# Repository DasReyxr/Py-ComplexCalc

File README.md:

# Py-ComplexCalc

**A complete ecosystem for solving n×n complex linear systems (Ax=b)** with both desktop GUI and embedded hardware solutions.

**Solve Ax=b instantly** with dual-format output (polar & rectangular), flexible input, and full system persistence.

```
Py-ComplexCalc/
├── Software Version/          # Desktop GUI application
│   ├── code/                  # Python source files
│   │   ├── UI_ComplexCalc.py  # Main GUI (customtkinter)
│   │   ├── ComplexCalc.py     # Core solver & parsing logic
│   │   ├── HK.jpg             # UI background
│   │   └── IE.png             # Logo icon
│   ├── doc/                   # Documentation
│   └── README.md              # Software-specific guide
│
├── HW Version/                # Embedded microcontroller solutions
│   ├── code/
│   │   ├── BlackPill STM32F411CE/    # Implementation for BlackPill
│   │   └── RayPill STM32F446ZE/      # Implementation for RayPill
│   ├── HW Files Schematic & Design/  # PCB schematics, layouts
│   └── (README coming soon)
│
├── OtherCalcs/                # Alternative implementations
├── LICENSE                    # MIT License
└── README.md          # This file
```

## ✨ Features

- **🔢 Dual Input Format**
  - Rectangular: `3+4j`, `-j2`, `5` (supports both `i` and `j` for imaginary unit)
  - Phasor: `10L30`, `5L-90°`, `3L0` (polar notation with degree angles)
  - Mix both formats in the same system
- **📊 Dual-Format Output**
  - Solutions shown in **polar** and **rectangular** simultaneously
- **🌓 Multiple Themes**
  - Dark, Light, Pink, Mint, Purple, Ocean — toggle anytime
- **💾 System Persistence**
  - Auto-save/load all computed systems
  - **File menu**: save current system, import from file, load saved system, refresh list
  - Export results (`.py`, `.txt`)
  - Session history with timestamps
- **🎯 Dynamic Matrix Sizing**
  - Solve 1×1 up to 10×10 systems
- **🧮 Built-in Calculator**
  - Quick complex-number scratchpad with backspace support
- **🚀 Standalone Executables**
  - Windows `.exe` and Linux binary — no Python install needed (see [Releases](https://github.com/DasReyxr/Py-ComplexCalc/releases))

---

## ℹ️ About

| | |
|---|---|
| **Version** | 4.00 |
| **Last updated** | 2026-08-21 |
| **Repository** | [github.com/DasReyxr/Py-ComplexCalc](https://github.com/DasReyxr/Py-ComplexCalc) |
| **Institution** | Universidad Autónoma de Aguascalientes |
| **Department** | Ingeniería en Electrónica |

Also available inside the app itself: **Help → About Complex Calc...**

---

## 🚀 Quick Start

### Option 1: Standalone Executable

1. Download `UI_ComplexCalc.exe` (Windows) or `UI_ComplexCalc` (Linux) from the latest [Release](https://github.com/DasReyxr/Py-ComplexCalc/releases).
2. Run it directly. No dependencies needed.

### Option 2: Run from Source

**Requirements:** Python 3.8+ (tested on 3.10, 3.11)

```bash
# Clone the repo
git clone https://github.com/DasReyxr/Py-ComplexCalc.git
cd Py-ComplexCalc/code

# (Optional) Create virtual environment
python -m venv .venv
source .venv/bin/activate  # Linux/macOS
# or: .\.venv\Scripts\Activate  # Windows PowerShell

# Install dependencies
pip install -r requirements.txt

# Run the app
python UI_ComplexCalc.py
```

---

## 📝 Input Format Guide

| Format         | Examples         | Notes                                 |
|---------------|------------------|---------------------------------------|
| Rectangular   | `3+4j`, `-j2`, `5` | Supports `i` and `j` for imaginary unit |
| Phasor        | `10L30`, `5L-90°`, `3L0` | Polar notation, degree angles         |
| Mixed         | Any combination   | Rows/columns can mix formats          |

### Example: Solving a 3×3 Complex System

**Problem:** Solve Ax = b where:
```
A = [2+1i    -1      0   ]      b = [1  ]
    [-1    2+0.5i  -1  ]          [0  ]
    [0      -1      2   ]          [1i ]
```

**Steps:**
1. Launch the app
2. Select **3×3** from size dropdown
3. Enter matrix A and vector b values (any format)
4. Click **Solve**
5. View results in both forms

**Output:**
```
x₁ = 0.8 + 0.6j  (Rectangular)
   = 1.0 ∠ 36.87° (Polar)

x₂ = 0.4 + 0.2j
   = 0.447 ∠ 26.57°

x₃ = 0.2 - 0.4j
   = 0.447 ∠ -63.43°
```

---

## 🛠️ Building a Standalone Executable (Windows & Linux)

PyInstaller builds a native executable for whatever OS you run it on — it
does **not** cross-compile, so a Windows `.exe` must be built on Windows
and a Linux binary must be built on Linux. This repo's GitHub Actions
workflow (`.github/workflows/build.yml`) does both automatically — trigger
it manually from the **Actions** tab, or push a tag like `v4.1` to also
publish a Release.

To build locally:

```bash
pip install pyinstaller
cd code
pyinstaller UI_ComplexCalc.spec
# Output: code/dist/UI_ComplexCalc(.exe on Windows)
```

---

## 📂 Project Structure

```
Py-ComplexCalc/
├── code/
│   ├── UI_ComplexCalc.py      # Main GUI (customtkinter)
│   ├── ComplexCalc.py         # Core solver & parsing logic
│   ├── UI_ComplexCalc.spec    # PyInstaller build spec
│   ├── requirements.txt       # Python dependencies
│   ├── HK.jpg                 # UI background / window icon
│   ├── IE.png                 # Institution logo
│   └── themes.json            # Color theme definitions
├── tests/
│   └── test_complexcalc_core.py  # Parser/solver robustness tests
├── doc/                        # Manuals
├── images/                     # README screenshots
└── LICENSE
```

---

## 🧪 Tests

Robustness tests for the parser, solver and persistence core (malformed
input, singular matrices, out-of-range sizes) — no extra dependencies:

```bash
python3 -m unittest discover -s tests -v
```

---

## 📋 Dependencies

| Package         | Purpose                                 |
|-----------------|-----------------------------------------|
| `numpy`         | Linear algebra (Gaussian elimination)   |
| `customtkinter` | Modern, theme-aware GUI widgets         |
| `pillow`        | Image loading for UI assets             |

**Install all at once:**
```bash
pip install -r code/requirements.txt
```

---

## 🎨 Customization

- **Change Theme Colors:** Edit `code/themes.json`.
- **Custom Images:** Replace `HK.jpg` and `IE.png` with your own (same filenames).

---

## 🐛 Troubleshooting

| Problem                    | Solution                                                        |
|----------------------------|-----------------------------------------------------------------|
| GUI won't start            | Install/upgrade customtkinter: `pip install --upgrade customtkinter` |
| "Singular matrix" error    | Matrix A must be invertible. Check for duplicate/linearly dependent rows. |
| Parsing error              | Use `3+4j` (no spaces), `10L30` (not `10L30.5`).                |
| Images not loading         | Ensure `HK.jpg` and `IE.png` exist in the same folder as `UI_ComplexCalc.py`. |
| Executable blocked by antivirus | False positive (Windows). Add to antivirus whitelist or build from source. |

---

## 📞 Support & Contributions

- **Bug Reports:** [GitHub Issues](https://github.com/DasReyxr/Py-ComplexCalc/issues)
- **Feature Requests:** [GitHub Discussions](https://github.com/DasReyxr/Py-ComplexCalc/discussions)
- **Pull Requests:** Welcome! Fork, branch, and submit a PR.

### Roadmap
- [ ] CSV import/export for batch solving
- [ ] Phasor diagram real-time visualization
- [ ] Advanced matrix operations (eigenvalues, determinants)

---

## 👥 Credits

**Developers:**
- Iker Garcia — [ikergarcia450@gmail.com](mailto:ikergarcia450@gmail.com)
- Das Reyes — [das.reyxr@outlook.com](mailto:das.reyxr@outlook.com)

**Development Team:**
- **Das Reyes** — Lead developer, theming, Testing, documentation [das.reyxr@outlook.com](mailto:das.reyxr@outlook.com)
- **Iker Garcia** — GUI design, user experience, documentation [ikergarcia450@gmail.com](mailto:ikergarcia450@gmail.com)
- **Roberto Lopez** — PCB Design, core solver logic  
- **Kevin Lara** — Hardware integration, embedded systems

**Built With:**
- [NumPy](https://numpy.org/) — Numerical computing
- [CustomTkinter](https://github.com/TomSchimansky/CustomTkinter) — Modern UI toolkit
- [Pillow](https://python-pillow.org/) — Image processing
- [PyInstaller](https://pyinstaller.org/) — Executable packaging

---

## 📄 License

MIT License — See [LICENSE](./LICENSE) for details.

**TL;DR:** Use freely, attribute the authors, no warranty.

---

**For Electronics Engineers, By Electronics Engineers** ⚡

*"Solve complex systems instantly. Focus on the engineering that matters."*

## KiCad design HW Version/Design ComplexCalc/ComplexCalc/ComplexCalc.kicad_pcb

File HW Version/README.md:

# Hardware Version 🔌⚡

**Embedded n×n complex linear system solver for STM32 microcontrollers.**

Real-time computation of Ax=b problems directly on ARM-based hardware, perfect for **AC circuit analysis, impedance calculations, and embedded signal processing**.

---

## 🎯 Overview

This folder contains complete hardware implementations for solving complex linear systems on microcontroller platforms, with no external dependencies or desktop PC required.

**Key Advantages:**
- ⚡ Real-time computation on embedded hardware
- 💾 Onboard persistent storage
- 🔋 Low power consumption

---

## 📋 Supported Platforms

### **BlackPill STM32F411CE** ✅
```
📁 BlackPill STM32F411CE/

Platform Details:
├─ MCU: ARM Cortex-M4 @ 100 MHz
├─ RAM: 128 KB
├─ Flash: 512 KB
├─ USB: Full-Speed (480 Mbps)
├─ Peripherals: ADC, UART, SPI, I2C
├─ Typical Use: Budget-conscious, compact designs
└─ Status: Fully implemented ✓
```

**Perfect for:**
- Portable embedded instruments
- Compact circuit analysis tools
- Educational projects with size constraints
- Low-cost mass production

---

### **RayPill STM32F446ZE** 🔄
```
📁 RayPill STM32F446ZE/

Platform Details:
├─ MCU: ARM Cortex-M4 @ 180 MHz
├─ RAM: 192 KB
├─ Flash: 512 KB
├─ USB: High-Speed (480 Mbps)
├─ Peripherals: Multiple ADCs, UARTs, SPI, I2C, Ethernet
├─ Typical Use: High-performance applications
└─ Status: Fully implemented ✓
```

**Perfect for:**
- Multi-channel signal processing
- High-speed real-time systems
- Industrial instrumentation
- Network-connected devices

---

## 🚀 Quick Start

### **Step 1: Choose Your Platform**
- **Limited resources?** → BlackPill STM32F411CE
- **Need more power?** → RayPill STM32F446ZE

### **Step 2: Get the Code**
```bash
cd HW\ Version/code/BlackPill\ STM32F411CE/
# or
cd HW\ Version/code/RayPill\ STM32F446ZE/
```

### **Step 3: Build & Flash**

**Using STM32CubeIDE (Recommended):**
1. Open STM32CubeIDE
2. File → Open Projects from File System
3. Select the platform folder
4. Press `Build` (Ctrl+B)
5. Connect microcontroller via USB
6. Press `Run` (Ctrl+Alt+X) to flash

**Using Arm Compiler Toolchain:**
```bash
arm-none-eabi-gcc -mcpu=cortex-m4 -mthumb \
  -O2 -Wall -c main.c -o main.o

arm-none-eabi-ld main.o -o firmware.elf

arm-none-eabi-objcopy -O binary firmware.elf firmware.bin
```

### **Step 4: Connect & Use**

**Via UART (Serial Terminal):**
```
Device: COM3 (Windows) or /dev/ttyUSB0 (Linux)
Baud Rate: 115200
Data Bits: 8
Parity: None
Stop Bits: 1
Flow Control: None
```

---

## 📂 Folder Structure

```
HW Version/
├── code/
│   ├── BlackPill STM32F411CE/
│   │   ├── main.c                # Entry point
│   │   ├── solver.c/.h           # Linear solver implementation
│   │   ├── parser.c/.h           # Complex number parser
│   │   ├── uart_io.c/.h          # Serial communication
│   │   ├── storage.c/.h          # Persistent memory
│   │   ├── STM32F411_HAL.conf    # Cube configuration
│   │   └── Makefile
│   │
│   └── RayPill STM32F446ZE/
│       ├── main.c
│       ├── solver.c/.h
│       ├── parser.c/.h
│       ├── uart_io.c/.h
│       ├── storage.c/.h
│       ├── STM32F446_HAL.conf
│       └── Makefile
│
├── HW Files Schematic & Design/
│   ├── Schematics/               # KiCad/.pdf circuit diagrams
│   ├── PCB Layouts/              # Gerber files for manufacturing
│   ├── BOM.csv                   # Bill of Materials
│   └── Assembly Guide.md         # PCB assembly instructions
│
└── README.md                     # This file
```

---

## 🔧 Technical Details

### **Solver Algorithm**
- **Method:** Gaussian elimination with partial pivoting
- **Precision:** Double-precision floating-point (64-bit)
- **Maximum Size:** 10×10 systems (configurable)
- **Computation Time:** ~10-50 ms (BlackPill), ~5-25 ms (RayPill)

### **Input Format Support**
| Format | Example | Supported |
|--------|---------|-----------|
| **Rectangular** | `3+4j`, `-j2`, `5` | ✅ Yes |
| **Phasor** | `10L30`, `5L-90°` | ✅ Yes |
| **Mixed** | Both in same system | ✅ Yes |

### **Output Format**
Results automatically convert to:
- **Rectangular:** `a + bj` (real + imaginary parts)

---

## 🛠️ Hardware Requirements

### **Minimum Setup**

**For BlackPill:**
- 1× BlackPill STM32F411CE board
- 1× USB-C cable (power & programming)
- 1× Serial terminal software (PuTTY, Tera Term, etc.)

**For RayPill:**
- 1× RayPill STM32F446ZE board
- 1× USB-A cable (power & programming)
- 1× Serial terminal software
- Optional: Additional sensors/peripherals

### **Optional Accessories**
- Logic analyzer (debugging)
- Oscilloscope (signal verification)
- SWD debugger (advanced debugging)

---

## 🚨 Troubleshooting

### **Build Issues**

| Problem | Solution |
|---------|----------|
| **"arm-none-eabi-gcc not found"** | Install ARM GCC toolchain for your OS |
| **Cannot connect to CubeIDE** | Ensure STM32CubeIDE is installed with F4 MCU support |
| **Build errors in HAL** | Verify STM32CubeMX generated files match target MCU |

### **Runtime Issues**

| Problem | Solution |
|---------|----------|
| **No serial output** | Check UART pins & baud rate (115200) |
| **"Singular matrix" error** | Matrix A must be invertible; add small diagonal term if needed |
| **Parsing error on input** | Use format `3+4j` (no spaces), `10L30` (not degrees symbol) |
| **System won't flash** | Ensure USB cable supports data transfer; try different port |

---

## 📊 Performance Comparison

| Metric | BlackPill F411 | RayPill F446 |
|--------|----------------|--------------|
| **Clock Speed** | 100 MHz | 180 MHz |
| **RAM** | 128 KB | 192 KB |
| **Flash** | 512 KB | 512 KB |
| **Solve Time (3×3)** | ~25 ms | ~12 ms |
| **Solve Time (10×10)** | ~200 ms | ~80 ms |
| **USB Speed** | Full-Speed | High-Speed |
| **Power Draw** | ~25 mA idle | ~45 mA idle |

---

## 🔌 Pinout Reference

## 📚 Additional Resources

- **[STM32F411 Datasheet](https://www.st.com/resource/en/datasheet/stm32f411ce.pdf)** — Complete hardware specs
- **[STM32F446 Datasheet](https://www.st.com/resource/en/datasheet/stm32f446ze.pdf)** — Complete hardware specs
- **[STM32CubeIDE Setup Guide](https://www.st.com/en/development-tools/stm32cubeide.html)** — IDE download & installation
- **[ARM CMSIS-DSP Library](https://github.com/ARM-software/CMSIS_5)** — Optimized math library
- **[Keil Compiler Documentation](https://www2.keil.com/mdk5)** — ARM compiler details

---

## 🐛 Known Limitations

- **Matrix Size:** Limited to 10×10 by design (RAM constraint on BlackPill)
- **Precision:** Double-precision (64-bit) floating-point accuracy
- **Complex Numbers:** No quaternions or higher algebras (future feature)
- **Visualization:** No built-in display output 

---

## 🤝 Contributing

Want to add support for more platforms? We'd love your help!

**How to contribute:**
1. Create a new folder: `code/YourMCU_Name/`
2. Implement `solver.c`, `parser.c`, `uart_io.c`, `storage.c`
3. Add build instructions and testing results
4. Submit a pull request with documentation

**Planned Goals:**
- [ ] Support for STM32F
- [ ] Optimize the code
- [ ] Clean the code
- [ ] Compile the Hex for easy uploading
- [ ] Upload the Designing files (Open Hardware) 

---

## 📞 Support & Issues

- **Bug Reports:** [GitHub Issues](https://github.com/DasReyxr/Py-ComplexCalc/issues)
- **Hardware Questions:** Open an issue with `[HARDWARE]` tag
- **Schematics:** Check `HW Files Schematic & Design/`
- **Build Help:** Include your MCU, IDE, and error message

---

## 📄 License

MIT License — See [../LICENSE](../LICENSE) for details.

---

## 🎯 Quick Links

| Resource | Location |
|----------|----------|
| **Main README** | [../README_GENERAL.md](../README_GENERAL.md) |
| **Software Version** | [../Software%20Version/](../Software%20Version/) |
| **Schematics** | [HW%20Files%20Schematic%20&%20Design/](HW%20Files%20Schematic%20%26%20Design/) |
| **GitHub** | [DasReyxr/Py-ComplexCalc](https://github.com/DasReyxr/Py-ComplexCalc) |

---

**For Electronics Engineers, By Electronics Engineers** ⚡

*"Embedded linear algebra solver. No PC required."*

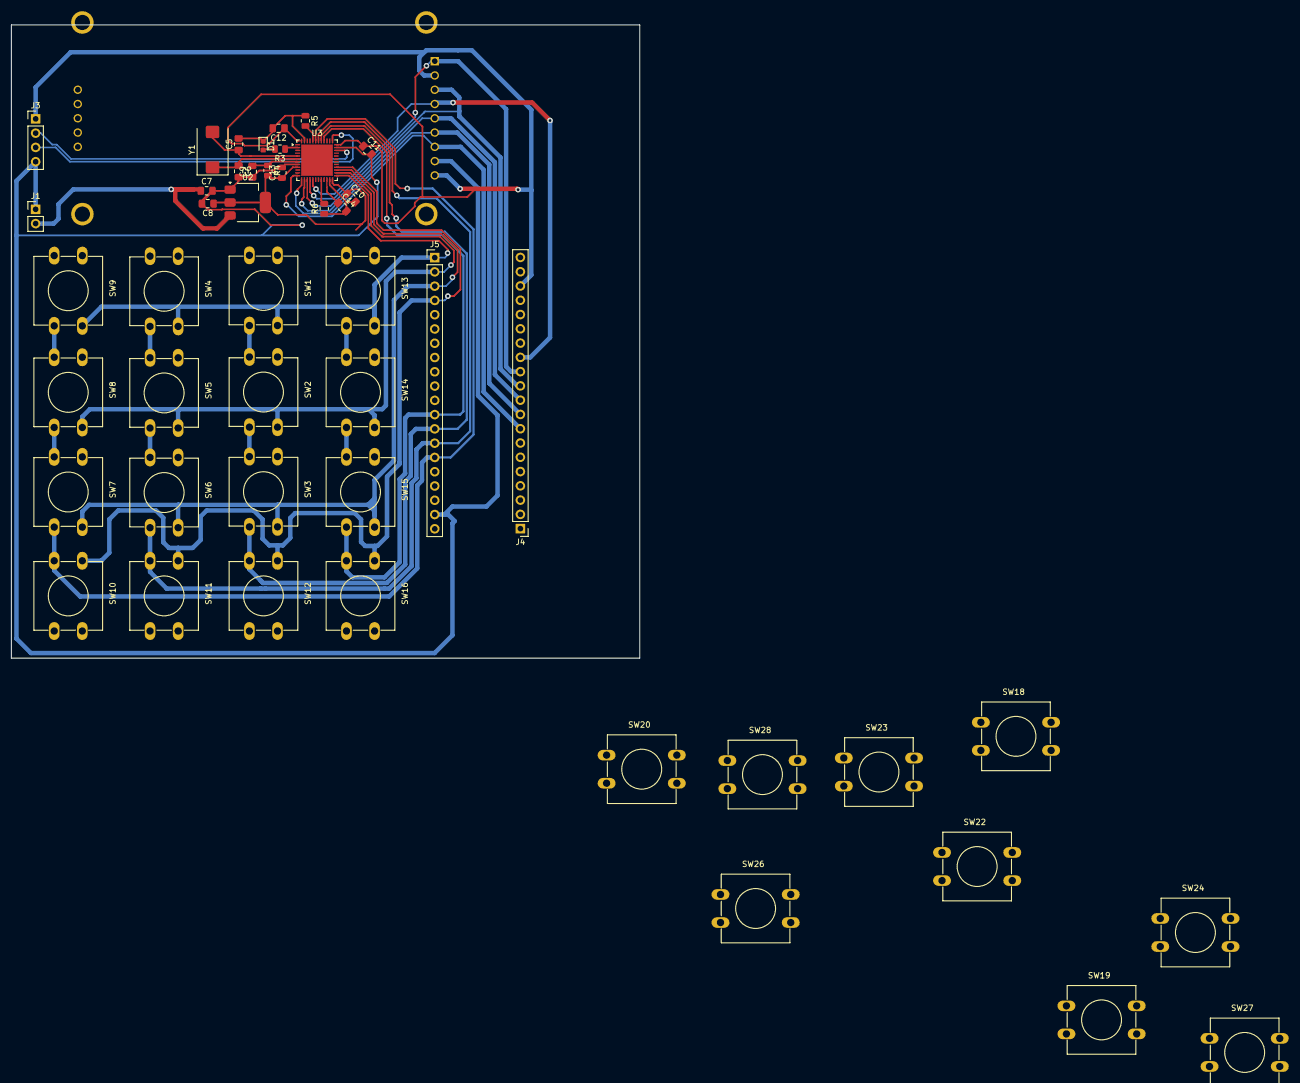
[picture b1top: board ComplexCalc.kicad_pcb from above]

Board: 2 copper layers, 111.8 x 112.7 mm, 48 parts (1 on the bottom side), 46 nets.

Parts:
C5, C6: 22pF; C_0805_2012Metric_Pad1.18x1.45mm_HandSolder
C7: 10uF; C_0805_2012Metric_Pad1.18x1.45mm_HandSolder
C8: 22uF; C_0805_2012Metric_Pad1.18x1.45mm_HandSolder
C9: 1uF; C_0805_2012Metric_Pad1.18x1.45mm_HandSolder
C10, C11, C12: 100nF; C_0805_2012Metric_Pad1.18x1.45mm_HandSolder
C13: 1uF; C_0805_2012Metric
C14: 2.2uF; C_0805_2012Metric_Pad1.18x1.45mm_HandSolder
D1: LED; LED_0603_1608Metric
J1: V_Battery; PinHeader_1x02_P2.54mm_Vertical
J2: Conn_01x09; CR2013-MI2120
J3: STLINK; PinHeader_1x04_P2.54mm_Vertical
J4, J5: Conn_01x20_Socket; PinHeader_1x20_P2.54mm_Vertical
R3: 220; R_0805_2012Metric
R4, R5, R6: 10k; R_0805_2012Metric
SW1: 4; SW_PUSH-12mm
SW2: 5; SW_PUSH-12mm
SW3: 6; SW_PUSH-12mm
SW4: 1; SW_PUSH-12mm
SW5: 2; SW_PUSH-12mm
SW6: 3; SW_PUSH-12mm
SW7: =; SW_PUSH-12mm
SW8: .; SW_PUSH-12mm
SW9: 0; SW_PUSH-12mm
SW10: -; SW_PUSH-12mm
SW11: del; SW_PUSH-12mm
SW12: <-; SW_PUSH-12mm
SW13: 7; SW_PUSH-12mm
SW14: 8; SW_PUSH-12mm
SW15: 9; SW_PUSH-12mm
SW16: M; SW_PUSH-12mm
SW18, SW20, SW26, SW28: MOD; SW_PUSH-12mm
SW19: <; SW_PUSH-12mm
SW22: ^; SW_PUSH-12mm
SW23: OK; SW_PUSH-12mm
SW24: v; SW_PUSH-12mm
SW27: >; SW_PUSH-12mm
U2: AMS1117-3.3; SOT-223-3_TabPin2
U3: STM32F411CEUx; QFN-48-1EP_7x7mm_P0.5mm_EP5.6x5.6mm
Y1: 8MHz; Crystal_SMD_EuroQuartz_MQ2-2Pin_7.0x5.0mm

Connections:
3.3V: C8.1, C10.1, C11.1, C12.1, C13.1, J2.2, J2.9, J3.1, J4.18, J5.20, R4.2, U2.2 (VO), U3.9 (VDDA), U3.24 (VDD), U3.36 (VDD), U3.48 (VDD)
5V: J4.20, J5.18
A0: J4.6, U3.10 (PA0)
A1: J4.7, U3.11 (PA1)
A2: J2.7, J4.8, U3.12 (PA2)
A3: J2.6, J4.9, U3.13 (PA3)
A4: J2.5, J4.10, U3.14 (PA4)
A5: J2.3, J4.11, U3.15 (PA5)
A6: J2.1, J4.12, U3.16 (PA6)
A7: J2.4, J4.13, U3.17 (PA7)
A8: J5.5, U3.29 (PA8)
A9: J5.6, U3.30 (PA9)
A10: J5.7, U3.31 (PA10)
A11: J5.8, U3.32 (PA11)
A12: J5.9, U3.33 (PA12)
A15: J5.10, U3.38 (PA15)
B0: J4.14, U3.18 (PB0)
B3: J5.11, U3.39 (PB3)
B4: J5.12, SW13.2, SW14.2, SW15.2, SW16.2, U3.40 (PB4)
B5: J5.13, SW1.2, SW2.2, SW3.2, SW12.2, U3.41 (PB5)
B6: J5.14, SW4.2, SW5.2, SW6.2, SW11.2, U3.42 (PB6)
B7: J5.15, SW7.2, SW8.2, SW9.2, SW10.2, U3.43 (PB7)
B8: J5.16, U3.45 (PB8)
B10: J4.17, U3.21 (PB10)
B12: J5.1, SW1.1, SW4.1, SW9.1, SW13.1, U3.25 (PB12)
B13: J5.2, SW2.1, SW5.1, SW8.1, SW14.1, U3.26 (PB13)
B14: J5.3, SW3.1, SW6.1, SW7.1, SW15.1, U3.27 (PB14)
B15: J5.4, SW10.1, SW11.1, SW12.1, SW16.1, U3.28 (PB15)
C13: R3.1, U3.2 (PC13)
COL5: SW18.1, SW19.1, SW20.1
COL6: SW22.1, SW23.1, SW24.1
COL7: SW26.1, SW27.1, SW28.1
GND: C5.2, C6.2, C7.2, C8.2, C9.1, C10.2, C11.2, C12.2, C13.2, C14.2, D1.1 (K), J1.1, J2.8, J3.4, J4.19, J5.17, J5.19, R5.1, R6.1, U2.1 (GND), U3.8 (VSSA), U3.23 (VSS), U3.35 (VSS), U3.47 (VSS), U3.49 (VSS)
NRST: C9.2, R4.1, U3.7 (NRST)
unnamed: D1.2 (A), R3.2
unnamed: R5.2, U3.44 (BOOT0)
unnamed: R6.2, U3.20 (PB2)
unnamed: C14.1, U3.22 (VCAP1)
OSC_IN: C5.1, U3.5 (PH0), Y1.2
OSC_OUT: C6.1, U3.6 (PH1), Y1.1
ROW5: SW18.2, SW22.2, SW26.2
ROW6: SW19.2, SW23.2, SW27.2
ROW7: SW20.2, SW24.2, SW28.2
SWCLK: J3.3, U3.37 (PA14)
SWDIO: J3.2, U3.34 (PA13)
VIN: C7.1, J1.2, U2.3 (VI)

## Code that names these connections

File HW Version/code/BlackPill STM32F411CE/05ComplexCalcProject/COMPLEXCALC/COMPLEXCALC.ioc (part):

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Mcu.Name=STM32F411C(C-E)Ux
Mcu.Package=UFQFPN48
Mcu.UserName=STM32F411CEUx
PA3.GPIOParameters=GPIO_Speed,GPIO_PuPd,GPIO_Label
PA3.GPIO_Label=CS
PA3.GPIO_PuPd=GPIO_NOPULL
PA3.GPIO_Speed=GPIO_SPEED_FREQ_VERY_HIGH
PA3.Signal=GPIO_Output
PA4.GPIOParameters=GPIO_Speed,GPIO_PuPd,GPIO_Label
PA4.GPIO_Label=DC
PA4.GPIO_PuPd=GPIO_NOPULL
PA4.GPIO_Speed=GPIO_SPEED_FREQ_VERY_HIGH
PA4.Signal=GPIO_Output
PA5.Mode=TX_Only_Simplex_Unidirect_Master
PA5.Signal=SPI1_SCK
PA6.GPIOParameters=GPIO_Speed,GPIO_Label
PA6.GPIO_Label=RES
PA6.GPIO_Speed=GPIO_SPEED_FREQ_VERY_HIGH
PA6.Signal=GPIO_Output
PA7.Mode=TX_Only_Simplex_Unidirect_Master
PA7.Signal=SPI1_MOSI
PB10.GPIOParameters=GPIO_PuPd
PB10.GPIO_PuPd=GPIO_PULLUP
PB10.Signal=GPIO_Input
PB12.GPIOParameters=GPIO_PuPd
PB12.GPIO_PuPd=GPIO_PULLUP
PB12.Signal=GPIO_Input
PB13.GPIOParameters=GPIO_PuPd
PB13.GPIO_PuPd=GPIO_PULLUP
PB13.Signal=GPIO_Input
PB14.GPIOParameters=GPIO_PuPd
PB14.GPIO_PuPd=GPIO_PULLUP
PB14.Signal=GPIO_Input
PB15.GPIOParameters=GPIO_PuPd
PB15.GPIO_PuPd=GPIO_PULLUP
PB15.Signal=GPIO_Input
PB6.GPIOParameters=GPIO_Speed
PB6.GPIO_Speed=GPIO_SPEED_FREQ_VERY_HIGH
PB6.Signal=GPIO_Output
PB7.GPIOParameters=GPIO_Speed
PB7.GPIO_Speed=GPIO_SPEED_FREQ_VERY_HIGH
PB7.Signal=GPIO_Output
PB8.GPIOParameters=GPIO_Speed
PB8.GPIO_Speed=GPIO_SPEED_FREQ_VERY_HIGH
PB8.Signal=GPIO_Output
PB9.GPIOParameters=GPIO_Speed
PB9.GPIO_Speed=GPIO_SPEED_FREQ_VERY_HIGH
PB9.Signal=GPIO_Output
PH0\ -\ OSC_IN.Mode=HSE-External-Oscillator
PH0\ -\ OSC_IN.Signal=RCC_OSC_IN
PH1\ -\ OSC_OUT.Mode=HSE-External-Oscillator
PH1\ -\ OSC_OUT.Signal=RCC_OSC_OUT
RCC.HSE_VALUE=25000000
RCC.SYSCLKFreq_VALUE=100000000
RCC.SYSCLKSource=RCC_SYSCLKSOURCE_PLLCLK
board=custom

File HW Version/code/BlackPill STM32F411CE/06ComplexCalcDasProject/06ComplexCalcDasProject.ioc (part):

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Mcu.Name=STM32F411C(C-E)Ux
Mcu.Package=UFQFPN48
Mcu.UserName=STM32F411CEUx
PA2.GPIOParameters=PinState,GPIO_Label
PA2.GPIO_Label=SCREEN_CS
PA2.PinState=GPIO_PIN_SET
PA2.Signal=GPIO_Output
PA3.GPIOParameters=GPIO_Label
PA3.GPIO_Label=SCREEN_RST
PA3.Signal=GPIO_Output
PA4.GPIOParameters=GPIO_Label
PA4.GPIO_Label=SCREEN_D/C
PA4.Signal=GPIO_Output
PA5.Mode=Full_Duplex_Master
PA5.Signal=SPI1_SCK
PA6.Mode=Full_Duplex_Master
PA6.Signal=SPI1_MISO
PA7.Mode=Full_Duplex_Master
PA7.Signal=SPI1_MOSI
PB12.GPIOParameters=GPIO_Label
PB12.GPIO_Label=COL1
PB12.Signal=GPIO_Input
PB13.GPIOParameters=GPIO_Label
PB13.GPIO_Label=COL2
PB13.Signal=GPIO_Input
PB14.GPIOParameters=GPIO_Label
PB14.GPIO_Label=COL3
PB14.Signal=GPIO_Input
PB15.GPIOParameters=GPIO_Label
PB15.GPIO_Label=COL4
PB15.Signal=GPIO_Input
PB4.GPIOParameters=GPIO_Label
PB4.GPIO_Label=ROW1
PB4.Signal=GPIO_Output
PB5.GPIOParameters=GPIO_Label
PB5.GPIO_Label=ROW2
PB5.Signal=GPIO_Output
PB6.GPIOParameters=GPIO_Label
PB6.GPIO_Label=ROW3
PB6.Signal=GPIO_Output
PB7.GPIOParameters=GPIO_Label
PB7.GPIO_Label=ROW4
PB7.Signal=GPIO_Output
RCC.HSE_VALUE=25000000
RCC.SYSCLKFreq_VALUE=16000000
board=custom

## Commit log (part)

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2025-08-19 Added python codes
2025-11-12 Created Project
2025-11-12 Updated calculator
2025-11-15 Pink mode
2025-11-15 Json files
2025-11-15 Added DasCalculator
2025-11-15 Added Eng calc
2025-11-22 Handle Expresions like j10
2025-11-22 Added Pink Mode
2025-11-22 Added IE png
2025-11-22 Restore LICENSE
2025-11-22 Minor changes
2025-11-25 Boring Version
2025-11-27 Re arranged Files
2025-11-27 Add readme
2025-11-29 Added Das Calc (Not Working Fractions)
2025-11-30 Created Exe
2025-11-30 Expanded division line
2025-12-17 Added Hardwave Version
2025-12-17 Moved Software version
2025-12-17 Merged 03Keiltest and complex calc
2025-12-17 Merged previous changes in 04ComplexCalcProjct
2025-12-17 Working keyboard, cant handle the lecture of multiple numbers
2025-12-29 Working System of eq, pending: corrupted matrix when going backward, print garbage, not implemented pink mode(yet)
2026-01-05 Added pink mode and minor fixes
2026-01-21 Pending to add Polar Button and Functions
2026-01-21 Moved Files
2026-01-21 Moved readme to SW version
2026-01-21 Added Readmes
2026-01-21 deleted previous readme general
2026-01-21 Modified Readme
2026-02-08 Add v2.7 features: integrated calculator, 6 color themes, improved window resizing
2026-02-12 Added a STM32CUBEIDE parameterized version called 05ComplexCalcProject and also we added a improvement of speed using the PLL at 180MHz
2026-02-12 Setupcolors to json
2026-02-12 Implemented Enter
2026-02-16 Se agrego el diseño preliminar de la calculadora
2026-04-24 Added icon to DasCalc
